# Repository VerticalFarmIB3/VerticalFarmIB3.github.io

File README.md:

Vertical farm - IB3 documentation and webpages

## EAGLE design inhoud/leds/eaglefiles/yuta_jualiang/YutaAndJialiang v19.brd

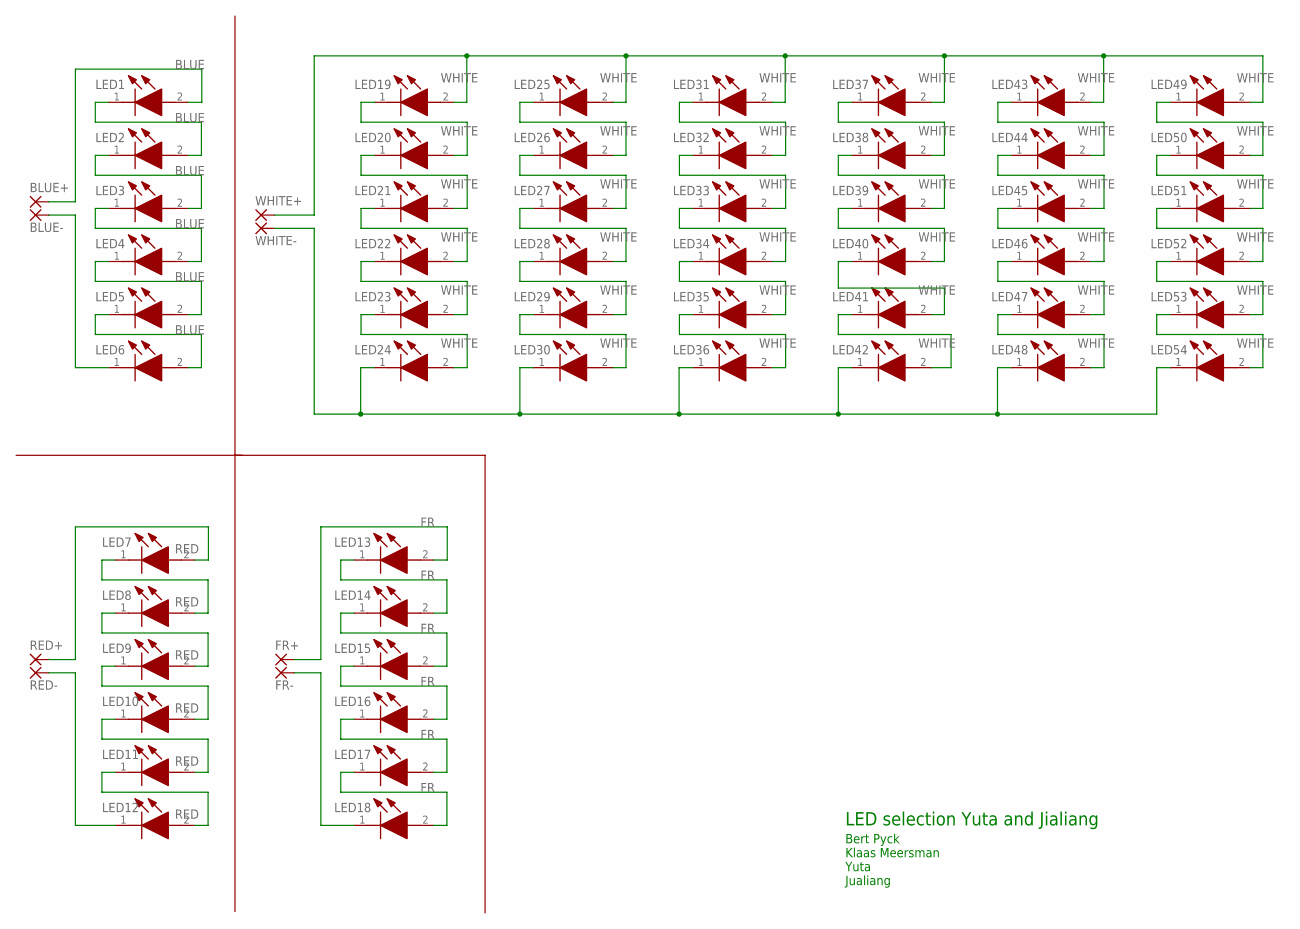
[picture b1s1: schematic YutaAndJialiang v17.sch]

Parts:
BLUE+: SOLDERPAD
BLUE-: SOLDERPAD
FR+: SOLDERPAD
FR-: SOLDERPAD
LED1, LED2, LED3, LED4, LED5, LED6: BLUE; L1SP-PNK1002800000
LED7, LED8, LED9, LED10, LED11, LED12: RED; L1SP-PNK1002800000
LED13, LED14, LED15, LED16, LED17, LED18: FR; L1SP-PNK1002800000
LED19, LED20, LED21, LED22, LED23, LED24, LED25, LED26, LED27, LED28, LED29, LED30, LED31, LED32, LED33, LED34, LED35, LED36, LED37, LED38, LED39, LED40, LED41, LED42, LED43, LED44, LED45, LED46, LED47, LED48, LED49, LED50, LED51, LED52, LED53, LED54: WHITE; L1SP-PNK1002800000
RED+: SOLDERPAD
RED-: SOLDERPAD
WHITE+: SOLDERPAD
WHITE-: SOLDERPAD

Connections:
unnamed: LED7.2 (A), RED+.1
unnamed: LED28.1 (K), LED29.2 (A)
unnamed: LED7.1 (K), LED8.2 (A)
unnamed: LED8.1 (K), LED9.2 (A)
unnamed: LED9.1 (K), LED10.2 (A)
unnamed: LED10.1 (K), LED11.2 (A)
unnamed: LED11.1 (K), LED12.2 (A)
unnamed: BLUE-.1, LED6.1 (K)
unnamed: FR+.1, LED13.2 (A)
unnamed: LED19.2 (A), LED25.2 (A), LED31.2 (A), LED37.2 (A), LED43.2 (A), LED49.2 (A), WHITE+.1
unnamed: LED24.1 (K), LED30.1 (K), LED36.1 (K), LED42.1 (K), LED48.1 (K), LED54.1 (K), WHITE-.1
unnamed: LED19.1 (K), LED20.2 (A)
unnamed: LED29.1 (K), LED30.2 (A)
unnamed: LED20.1 (K), LED21.2 (A)
unnamed: LED21.1 (K), LED22.2 (A)
unnamed: LED22.1 (K), LED23.2 (A)
unnamed: LED13.1 (K), LED14.2 (A)
unnamed: LED14.1 (K), LED15.2 (A)
unnamed: LED15.1 (K), LED16.2 (A)
unnamed: LED16.1 (K), LED17.2 (A)
unnamed: LED17.1 (K), LED18.2 (A)
unnamed: LED23.1 (K), LED24.2 (A)
unnamed: FR-.1, LED18.1 (K)
unnamed: LED25.1 (K), LED26.2 (A)
unnamed: LED26.1 (K), LED27.2 (A)
unnamed: LED27.1 (K), LED28.2 (A)
unnamed: LED12.1 (K), RED-.1
unnamed: LED31.1 (K), LED32.2 (A)
unnamed: LED32.1 (K), LED33.2 (A)
unnamed: BLUE+.1, LED1.2 (A)
unnamed: LED1.1 (K), LED2.2 (A)
unnamed: LED2.1 (K), LED3.2 (A)
unnamed: LED3.1 (K), LED4.2 (A)
unnamed: LED4.1 (K), LED5.2 (A)
unnamed: LED5.1 (K), LED6.2 (A)
unnamed: LED33.1 (K), LED34.2 (A)
unnamed: LED34.1 (K), LED35.2 (A)
unnamed: LED35.1 (K), LED36.2 (A)
unnamed: LED37.1 (K), LED38.2 (A)
unnamed: LED38.1 (K), LED39.2 (A)
unnamed: LED39.1 (K), LED40.2 (A)
unnamed: LED40.1 (K), LED41.2 (A)
unnamed: LED41.1 (K), LED42.2 (A)
unnamed: LED43.1 (K), LED44.2 (A)
unnamed: LED44.1 (K), LED45.2 (A)
unnamed: LED45.1 (K), LED46.2 (A)
unnamed: LED46.1 (K), LED47.2 (A)
unnamed: LED47.1 (K), LED48.2 (A)
unnamed: LED49.1 (K), LED50.2 (A)
unnamed: LED50.1 (K), LED51.2 (A)
unnamed: LED51.1 (K), LED52.2 (A)
unnamed: LED52.1 (K), LED53.2 (A)
unnamed: LED53.1 (K), LED54.2 (A)

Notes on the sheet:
LED selection Yuta and Jialiang
Bert Pyck Klaas Meersman Yuta Jualiang

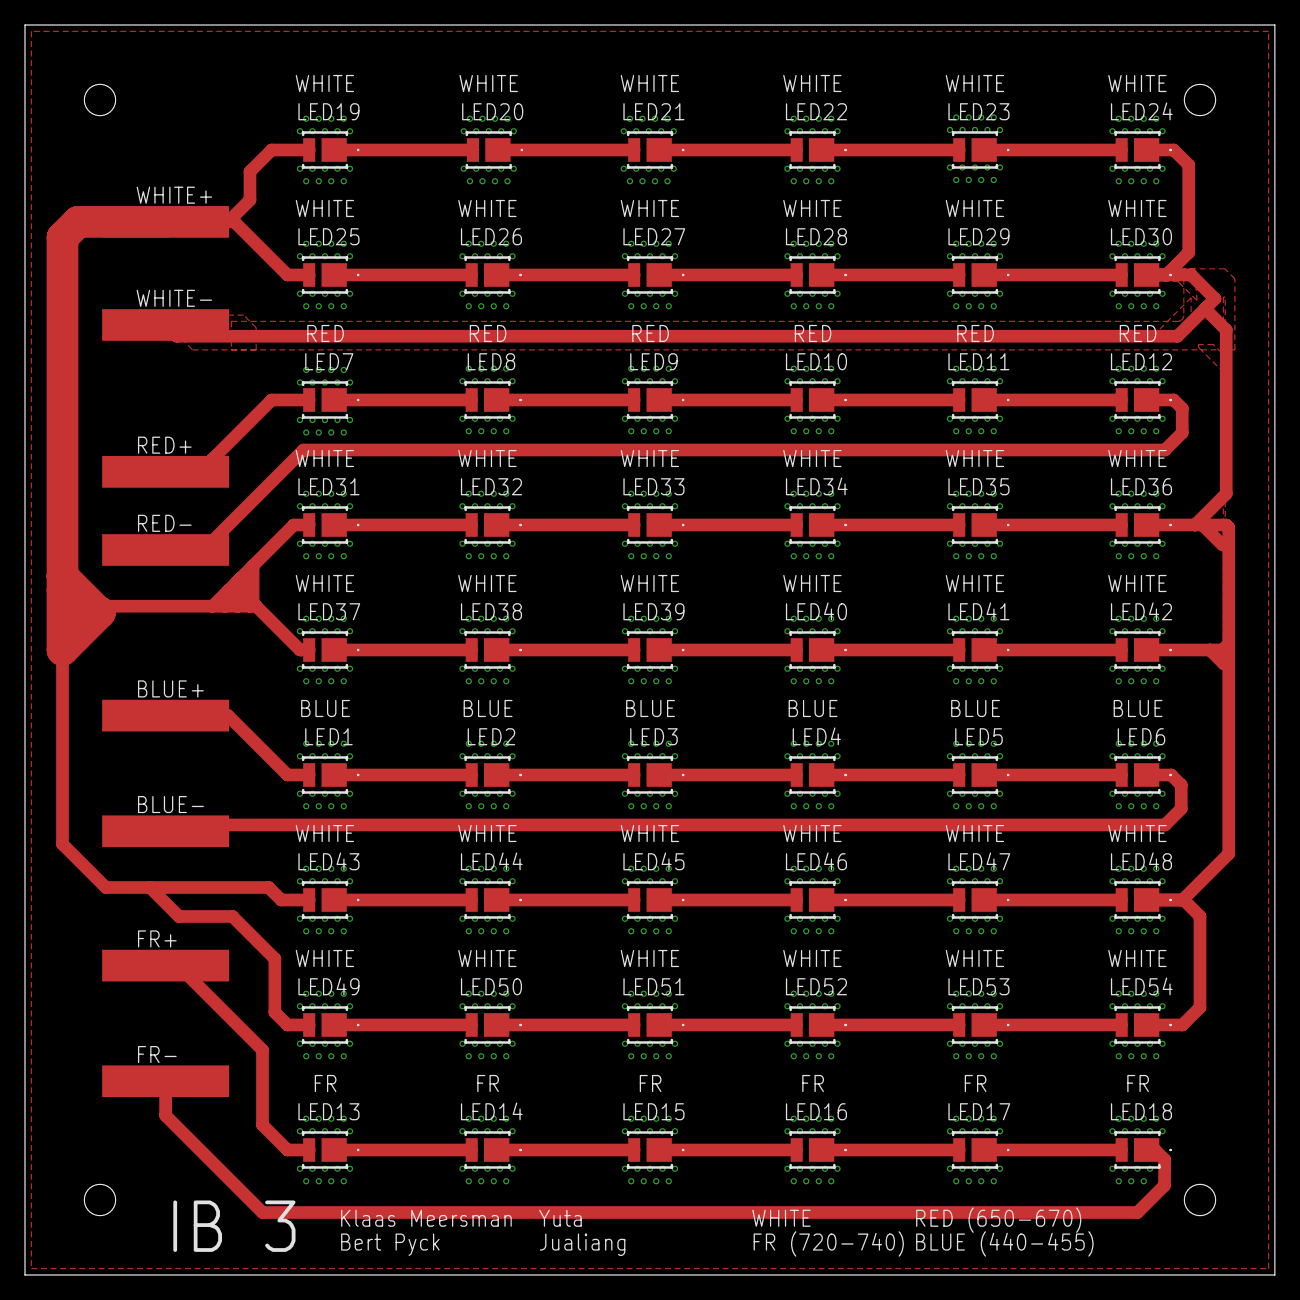
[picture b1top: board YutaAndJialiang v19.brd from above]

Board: 2 copper layers, 100.0 x 100.0 mm, 62 parts (0 on the bottom side), 53 nets.

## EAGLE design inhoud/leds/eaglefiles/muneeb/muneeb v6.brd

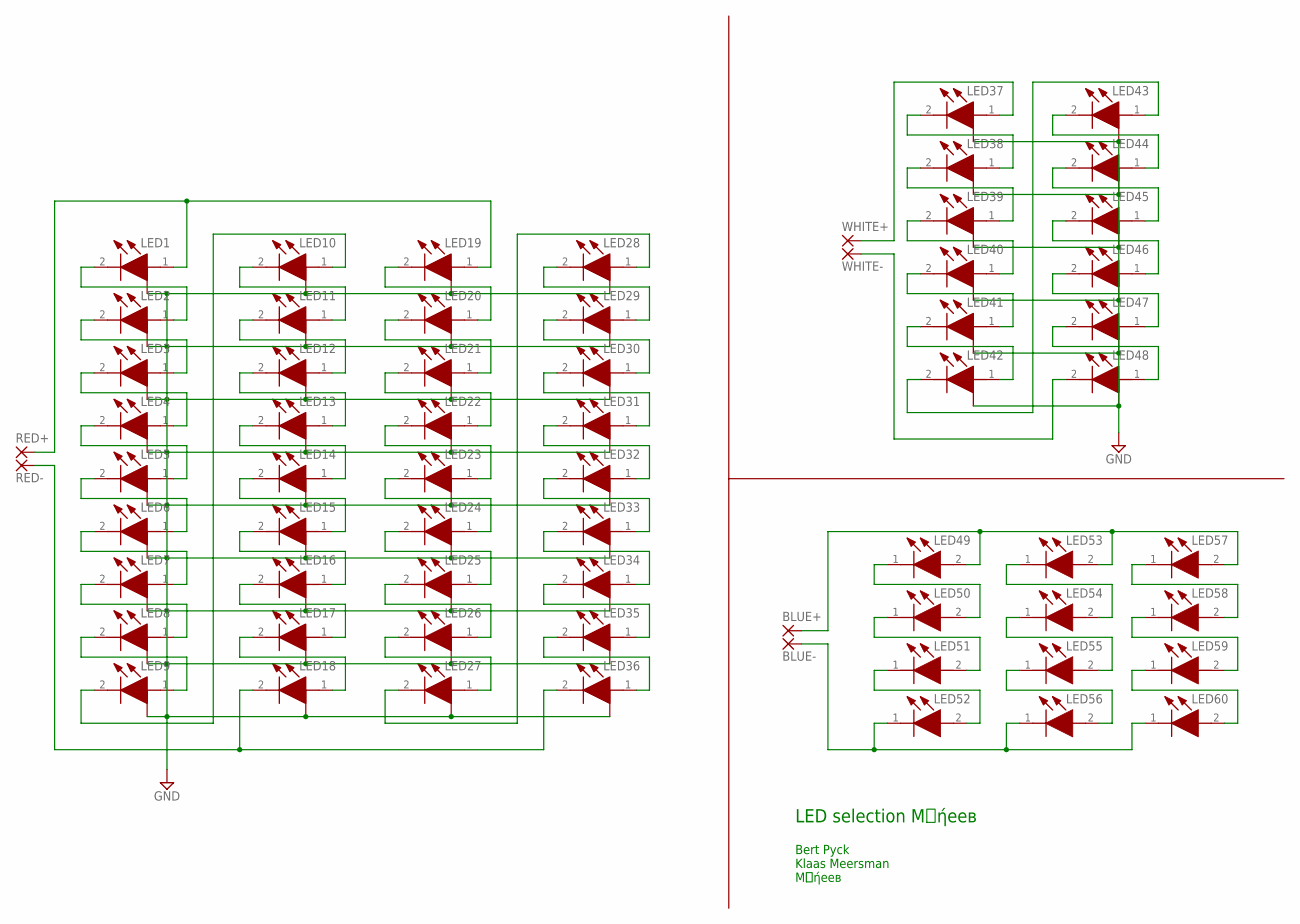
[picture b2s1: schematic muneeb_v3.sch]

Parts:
BLUE+: SOLDERPAD
BLUE-: SOLDERPAD
LED1, LED2, LED3, LED4, LED5, LED6, LED7, LED8, LED9, LED10, LED11, LED12, LED13, LED14, LED15, LED16, LED17, LED18, LED19, LED20, LED21, LED22, LED23, LED24, LED25, LED26, LED27, LED28, LED29, LED30, LED31, LED32, LED33, LED34, LED35, LED36: RED; GR_CSSRML.24
LED37, LED38, LED39, LED40, LED41, LED42, LED43, LED44, LED45, LED46, LED47, LED48: WHITE; GR_CSSRML.24
LED49, LED50, LED51, LED52, LED53, LED54, LED55, LED56, LED57, LED58, LED59, LED60: BLUE; GD_JTLPSI1.14
RED+: SOLDERPAD
RED-: SOLDERPAD
WHITE+: SOLDERPAD
WHITE-: SOLDERPAD

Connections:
GND: LED1.GND, LED1.P$1 (GND), LED1.P$3 (GND), LED1.P$5 (GND), LED1.P$6 (GND), LED1.P$7 (GND), LED1.P$8 (GND), LED1.P$9 (GND), LED1.P$11 (GND), LED1.P$12 (GND), LED1.P$13 (GND), LED1.P$14 (GND), LED1.P$15 (GND), LED2.GND, LED2.P$1 (GND), LED2.P$3 (GND), LED2.P$5 (GND), LED2.P$6 (GND), LED2.P$7 (GND), LED2.P$8 (GND), LED2.P$9 (GND), LED2.P$11 (GND), LED2.P$12 (GND), LED2.P$13 (GND), LED2.P$14 (GND), LED2.P$15 (GND), LED3.GND, LED3.P$1 (GND), LED3.P$3 (GND), LED3.P$5 (GND), LED3.P$6 (GND), LED3.P$7 (GND), LED3.P$8 (GND), LED3.P$9 (GND), LED3.P$11 (GND), LED3.P$12 (GND), LED3.P$13 (GND), LED3.P$14 (GND), LED3.P$15 (GND), LED4.GND, LED4.P$1 (GND), LED4.P$3 (GND), LED4.P$5 (GND), LED4.P$6 (GND), LED4.P$7 (GND), LED4.P$8 (GND), LED4.P$9 (GND), LED4.P$11 (GND), LED4.P$12 (GND), LED4.P$13 (GND), LED4.P$14 (GND), LED4.P$15 (GND), LED5.GND, LED5.P$1 (GND), LED5.P$3 (GND), LED5.P$5 (GND), LED5.P$6 (GND), LED5.P$7 (GND), LED5.P$8 (GND), LED5.P$9 (GND), LED5.P$11 (GND), LED5.P$12 (GND), LED5.P$13 (GND), LED5.P$14 (GND), LED5.P$15 (GND), LED6.GND, LED6.P$1 (GND), LED6.P$3 (GND), LED6.P$5 (GND), LED6.P$6 (GND), LED6.P$7 (GND), LED6.P$8 (GND), LED6.P$9 (GND), LED6.P$11 (GND), LED6.P$12 (GND), LED6.P$13 (GND), LED6.P$14 (GND), LED6.P$15 (GND), LED7.GND, LED7.P$1 (GND), LED7.P$3 (GND), LED7.P$5 (GND), LED7.P$6 (GND), LED7.P$7 (GND), LED7.P$8 (GND), LED7.P$9 (GND), LED7.P$11 (GND), LED7.P$12 (GND), LED7.P$13 (GND), LED7.P$14 (GND), LED7.P$15 (GND), LED8.GND, LED8.P$1 (GND), LED8.P$3 (GND), LED8.P$5 (GND), LED8.P$6 (GND), LED8.P$7 (GND), LED8.P$8 (GND), LED8.P$9 (GND), LED8.P$11 (GND), LED8.P$12 (GND), LED8.P$13 (GND), LED8.P$14 (GND), LED8.P$15 (GND), LED9.GND, LED9.P$1 (GND), LED9.P$3 (GND), LED9.P$5 (GND), LED9.P$6 (GND), LED9.P$7 (GND), LED9.P$8 (GND), LED9.P$9 (GND), LED9.P$11 (GND), LED9.P$12 (GND), LED9.P$13 (GND), LED9.P$14 (GND), LED9.P$15 (GND), LED10.GND, LED10.P$1 (GND), LED10.P$3 (GND), LED10.P$5 (GND), LED10.P$6 (GND), LED10.P$7 (GND), LED10.P$8 (GND), LED10.P$9 (GND), LED10.P$11 (GND), LED10.P$12 (GND), LED10.P$13 (GND), LED10.P$14 (GND), LED10.P$15 (GND), LED11.GND, LED11.P$1 (GND), LED11.P$3 (GND), LED11.P$5 (GND), LED11.P$6 (GND), LED11.P$7 (GND), LED11.P$8 (GND), LED11.P$9 (GND), LED11.P$11 (GND), LED11.P$12 (GND), LED11.P$13 (GND), LED11.P$14 (GND), LED11.P$15 (GND), LED12.GND, LED12.P$1 (GND), LED12.P$3 (GND), LED12.P$5 (GND), LED12.P$6 (GND), LED12.P$7 (GND), LED12.P$8 (GND), LED12.P$9 (GND), LED12.P$11 (GND), LED12.P$12 (GND), LED12.P$13 (GND), LED12.P$14 (GND), LED12.P$15 (GND), LED13.GND, LED13.P$1 (GND), LED13.P$3 (GND), LED13.P$5 (GND), LED13.P$6 (GND), LED13.P$7 (GND), LED13.P$8 (GND), LED13.P$9 (GND), LED13.P$11 (GND), LED13.P$12 (GND), LED13.P$13 (GND), LED13.P$14 (GND), LED13.P$15 (GND), LED14.GND, LED14.P$1 (GND), LED14.P$3 (GND), LED14.P$5 (GND), LED14.P$6 (GND), LED14.P$7 (GND), LED14.P$8 (GND), LED14.P$9 (GND), LED14.P$11 (GND), LED14.P$12 (GND), LED14.P$13 (GND), LED14.P$14 (GND), LED14.P$15 (GND), LED15.GND, LED15.P$1 (GND), LED15.P$3 (GND), LED15.P$5 (GND), LED15.P$6 (GND), LED15.P$7 (GND), LED15.P$8 (GND), LED15.P$9 (GND), LED15.P$11 (GND), LED15.P$12 (GND), LED15.P$13 (GND), LED15.P$14 (GND), LED15.P$15 (GND), LED16.GND, LED16.P$1 (GND), LED16.P$3 (GND), LED16.P$5 (GND), LED16.P$6 (GND), LED16.P$7 (GND), LED16.P$8 (GND), LED16.P$9 (GND), LED16.P$11 (GND), LED16.P$12 (GND), LED16.P$13 (GND), LED16.P$14 (GND), LED16.P$15 (GND), LED17.GND, LED17.P$1 (GND), LED17.P$3 (GND), LED17.P$5 (GND), LED17.P$6 (GND), LED17.P$7 (GND), LED17.P$8 (GND), LED17.P$9 (GND), LED17.P$11 (GND), LED17.P$12 (GND), LED17.P$13 (GND), LED17.P$14 (GND), LED17.P$15 (GND), LED18.GND, LED18.P$1 (GND), LED18.P$3 (GND), LED18.P$5 (GND), LED18.P$6 (GND), LED18.P$7 (GND), LED18.P$8 (GND), LED18.P$9 (GND), LED18.P$11 (GND), LED18.P$12 (GND), LED18.P$13 (GND), LED18.P$14 (GND), LED18.P$15 (GND), LED19.GND, LED19.P$1 (GND), LED19.P$3 (GND), LED19.P$5 (GND), LED19.P$6 (GND), LED19.P$7 (GND), LED19.P$8 (GND), LED19.P$9 (GND), LED19.P$11 (GND), LED19.P$12 (GND), LED19.P$13 (GND), LED19.P$14 (GND), LED19.P$15 (GND), LED20.GND, LED20.P$1 (GND), LED20.P$3 (GND), LED20.P$5 (GND), LED20.P$6 (GND), LED20.P$7 (GND), LED20.P$8 (GND), LED20.P$9 (GND), LED20.P$11 (GND), LED20.P$12 (GND), LED20.P$13 (GND), LED20.P$14 (GND), LED20.P$15 (GND), LED21.GND, LED21.P$1 (GND), LED21.P$3 (GND), LED21.P$5 (GND), LED21.P$6 (GND), LED21.P$7 (GND), LED21.P$8 (GND), LED21.P$9 (GND), LED21.P$11 (GND), LED21.P$12 (GND), LED21.P$13 (GND), LED21.P$14 (GND), LED21.P$15 (GND), LED22.GND, LED22.P$1 (GND), LED22.P$3 (GND), LED22.P$5 (GND), LED22.P$6 (GND), LED22.P$7 (GND), LED22.P$8 (GND), LED22.P$9 (GND), LED22.P$11 (GND), LED22.P$12 (GND), LED22.P$13 (GND), LED22.P$14 (GND), LED22.P$15 (GND), LED23.GND, LED23.P$1 (GND), LED23.P$3 (GND), LED23.P$5 (GND), LED23.P$6 (GND), LED23.P$7 (GND), LED23.P$8 (GND), LED23.P$9 (GND), LED23.P$11 (GND), LED23.P$12 (GND), LED23.P$13 (GND), LED23.P$14 (GND), LED23.P$15 (GND), LED24.GND, LED24.P$1 (GND), LED24.P$3 (GND), LED24.P$5 (GND), LED24.P$6 (GND), LED24.P$7 (GND), LED24.P$8 (GND), LED24.P$9 (GND), LED24.P$11 (GND), LED24.P$12 (GND), LED24.P$13 (GND), LED24.P$14 (GND), LED24.P$15 (GND), LED25.GND, LED25.P$1 (GND), LED25.P$3 (GND), LED25.P$5 (GND), LED25.P$6 (GND), LED25.P$7 (GND), LED25.P$8 (GND), LED25.P$9 (GND), LED25.P$11 (GND), LED25.P$12 (GND), LED25.P$13 (GND), LED25.P$14 (GND), LED25.P$15 (GND), LED26.GND, LED26.P$1 (GND), LED26.P$3 (GND), LED26.P$5 (GND), LED26.P$6 (GND), LED26.P$7 (GND), LED26.P$8 (GND), LED26.P$9 (GND), LED26.P$11 (GND), LED26.P$12 (GND), LED26.P$13 (GND), LED26.P$14 (GND), LED26.P$15 (GND), LED27.GND, LED27.P$1 (GND), LED27.P$3 (GND), LED27.P$5 (GND), LED27.P$6 (GND), LED27.P$7 (GND), LED27.P$8 (GND), LED27.P$9 (GND), LED27.P$11 (GND), LED27.P$12 (GND), LED27.P$13 (GND), LED27.P$14 (GND), LED27.P$15 (GND), LED28.GND, LED28.P$1 (GND), LED28.P$3 (GND), LED28.P$5 (GND), LED28.P$6 (GND), LED28.P$7 (GND), LED28.P$8 (GND), LED28.P$9 (GND), LED28.P$11 (GND), LED28.P$12 (GND), LED28.P$13 (GND), LED28.P$14 (GND), LED28.P$15 (GND), LED29.GND, LED29.P$1 (GND), LED29.P$3 (GND), LED29.P$5 (GND), LED29.P$6 (GND), LED29.P$7 (GND), LED29.P$8 (GND), LED29.P$9 (GND), LED29.P$11 (GND), LED29.P$12 (GND), LED29.P$13 (GND), LED29.P$14 (GND), LED29.P$15 (GND), LED30.GND, LED30.P$1 (GND), LED30.P$3 (GND), LED30.P$5 (GND), LED30.P$6 (GND), LED30.P$7 (GND), LED30.P$8 (GND), LED30.P$9 (GND), LED30.P$11 (GND), LED30.P$12 (GND), LED30.P$13 (GND), LED30.P$14 (GND), LED30.P$15 (GND), LED31.GND, LED31.P$1 (GND), LED31.P$3 (GND), LED31.P$5 (GND), LED31.P$6 (GND), LED31.P$7 (GND), LED31.P$8 (GND), LED31.P$9 (GND), LED31.P$11 (GND), LED31.P$12 (GND), LED31.P$13 (GND), LED31.P$14 (GND), LED31.P$15 (GND), LED32.GND, LED32.P$1 (GND), LED32.P$3 (GND), LED32.P$5 (GND), LED32.P$6 (GND), LED32.P$7 (GND), LED32.P$8 (GND), LED32.P$9 (GND), LED32.P$11 (GND), LED32.P$12 (GND), LED32.P$13 (GND), LED32.P$14 (GND), LED32.P$15 (GND), LED33.GND, LED33.P$1 (GND), LED33.P$3 (GND), LED33.P$5 (GND), LED33.P$6 (GND), LED33.P$7 (GND), LED33.P$8 (GND), LED33.P$9 (GND), LED33.P$11 (GND), LED33.P$12 (GND), LED33.P$13 (GND), LED33.P$14 (GND), LED33.P$15 (GND), LED34.GND, LED34.P$1 (GND), LED34.P$3 (GND), LED34.P$5 (GND), LED34.P$6 (GND), LED34.P$7 (GND), LED34.P$8 (GND), LED34.P$9 (GND), LED34.P$11 (GND), LED34.P$12 (GND), LED34.P$13 (GND), LED34.P$14 (GND), LED34.P$15 (GND), LED35.GND, LED35.P$1 (GND), LED35.P$3 (GND), LED35.P$5 (GND), LED35.P$6 (GND), LED35.P$7 (GND), LED35.P$8 (GND), LED35.P$9 (GND), LED35.P$11 (GND), LED35.P$12 (GND)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
unnamed: LED1.1 (A), LED19.1 (A), RED+.1
unnamed: LED1.2 (K), LED2.1 (A)
unnamed: LED37.1 (A), WHITE+.1
unnamed: LED48.2 (K), WHITE-.1
unnamed: LED37.2 (K), LED38.1 (A)
unnamed: LED38.2 (K), LED39.1 (A)
unnamed: LED39.2 (K), LED40.1 (A)
unnamed: LED40.2 (K), LED41.1 (A)
unnamed: LED41.2 (K), LED42.1 (A)
unnamed: LED42.2 (K), LED43.1 (A)
unnamed: LED2.2 (K), LED3.1 (A)
unnamed: LED3.2 (K), LED4.1 (A)
unnamed: LED4.2 (K), LED5.1 (A)
unnamed: LED5.2 (K), LED6.1 (A)
unnamed: LED6.2 (K), LED7.1 (A)
unnamed: LED43.2 (K), LED44.1 (A)
unnamed: LED44.2 (K), LED45.1 (A)
unnamed: LED45.2 (K), LED46.1 (A)
unnamed: LED46.2 (K), LED47.1 (A)
unnamed: BLUE+.1, LED49.2 (A), LED53.2 (A), LED57.2 (A)
unnamed: LED7.2 (K), LED8.1 (A)
unnamed: BLUE-.1, LED52.1 (K), LED56.1 (K), LED60.1 (K)
unnamed: LED8.2 (K), LED9.1 (A)
unnamed: LED10.2 (K), LED11.1 (A)
unnamed: LED11.2 (K), LED12.1 (A)
unnamed: LED12.2 (K), LED13.1 (A)
unnamed: LED13.2 (K), LED14.1 (A)
unnamed: LED49.1 (K), LED50.2 (A)
unnamed: LED19.2 (K), LED20.1 (A)
unnamed: LED20.2 (K), LED21.1 (A)
unnamed: LED50.1 (K), LED51.2 (A)
unnamed: LED51.1 (K), LED52.2 (A)
unnamed: LED53.1 (K), LED54.2 (A)
unnamed: LED14.2 (K), LED15.1 (A)
unnamed: LED15.2 (K), LED16.1 (A)
unnamed: LED16.2 (K), LED17.1 (A)
unnamed: LED17.2 (K), LED18.1 (A)
unnamed: LED54.1 (K), LED55.2 (A)
unnamed: LED55.1 (K), LED56.2 (A)
unnamed: LED57.1 (K), LED58.2 (A)
unnamed: LED58.1 (K), LED59.2 (A)
unnamed: LED59.1 (K), LED60.2 (A)
unnamed: LED47.2 (K), LED48.1 (A)
unnamed: LED18.2 (K), LED36.2 (K), RED-.1
unnamed: LED9.2 (K), LED10.1 (A)
unnamed: LED21.2 (K), LED22.1 (A)
unnamed: LED22.2 (K), LED23.1 (A)
unnamed: LED23.2 (K), LED24.1 (A)
unnamed: LED24.2 (K), LED25.1 (A)
unnamed: LED25.2 (K), LED26.1 (A)
unnamed: LED26.2 (K), LED27.1 (A)
unnamed: LED28.2 (K), LED29.1 (A)
unnamed: LED29.2 (K), LED30.1 (A)
unnamed: LED30.2 (K), LED31.1 (A)
unnamed: LED31.2 (K), LED32.1 (A)
unnamed: LED32.2 (K), LED33.1 (A)
unnamed: LED33.2 (K), LED34.1 (A)
unnamed: LED34.2 (K), LED35.1 (A)
unnamed: LED35.2 (K), LED36.1 (A)
unnamed: LED27.2 (K), LED28.1 (A)

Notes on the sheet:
LED selection M𝔲ήeeв
Bert Pyck Klaas Meersman M𝔲ήeeв

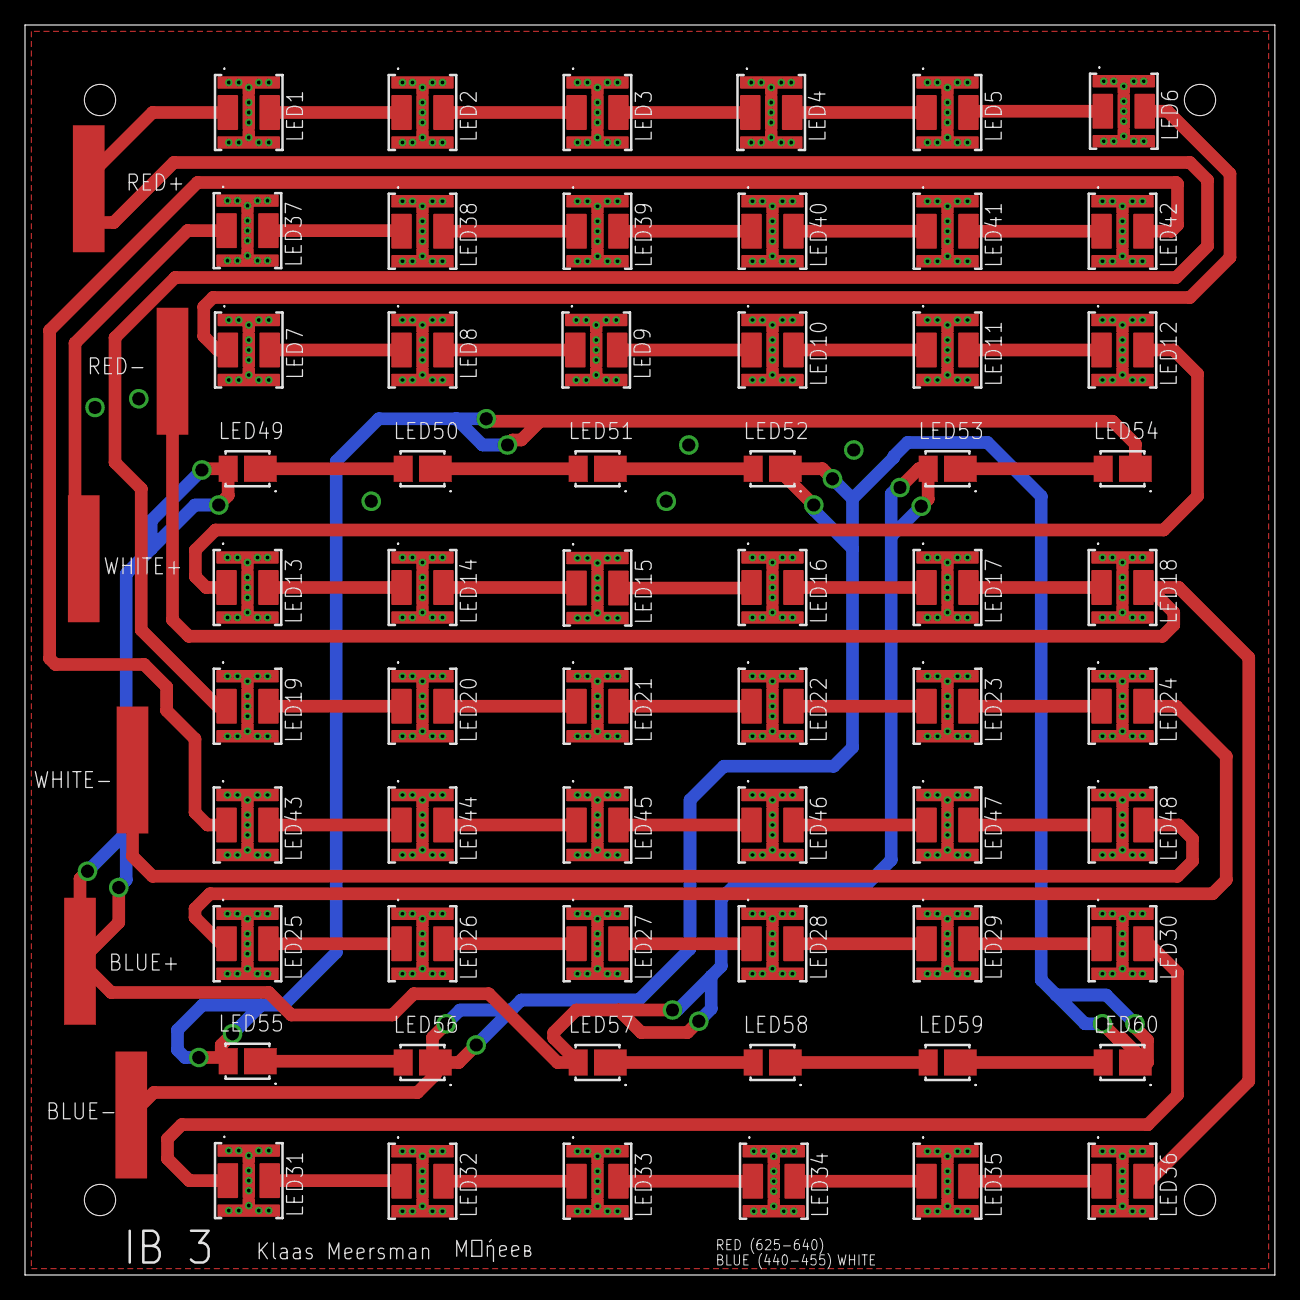
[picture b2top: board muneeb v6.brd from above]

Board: 2 copper layers, 100.0 x 100.0 mm, 66 parts (0 on the bottom side), 61 nets.

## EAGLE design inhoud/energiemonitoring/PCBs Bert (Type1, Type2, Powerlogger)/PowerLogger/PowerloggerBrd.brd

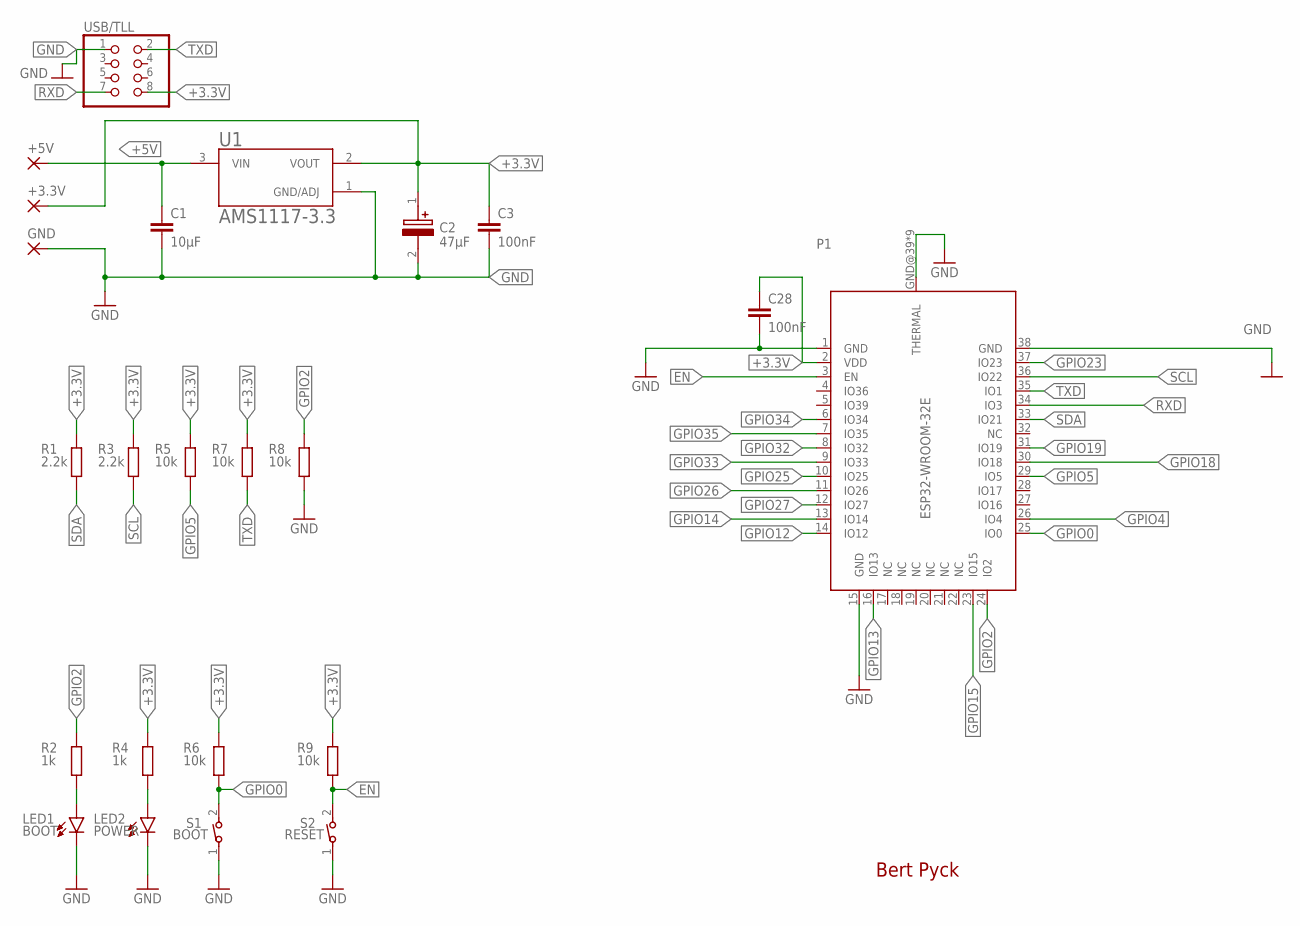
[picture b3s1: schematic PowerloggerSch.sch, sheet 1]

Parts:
+3.3V, +5V: SOLDERPAD
C1: 10µF; C1206
C2: 47µF; CAPAE660X550N
C3, C28: 100nF; C1206
GND: SOLDERPAD
LED1: BOOT; CHIPLED_1206
LED2: POWER; CHIPLED_1206
P1: ESP32-WROOM-32E
R1, R3: 2.2k; R1206
R2, R4: 1k; R1206
R5, R6, R7, R8, R9: 10k; R1206
S1: BOOT; 434111043826
S2: RESET; 434111043826
U1: AMS1117-3.3; SOT229P700X180-4N
USB/TLL: PINHD-2X4; 2X04

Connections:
+3.3V: +3.3V.1, C2.1 (+), C3.1, C28.1, P1.2 (VDD), R1.2, R3.2, R4.2, R5.2, R6.2, R7.2, R9.2, U1.2 (VOUT), USB/TLL.8; also elsewhere on the board
+5V: +5V.1, C1.1, U1.3 (VIN); also elsewhere on the board
EN: P1.3 (EN), R9.1, S2.2
GND: C1.2, C2.2 (-), C3.2, C28.2, GND.1, LED1.C, LED2.C, P1.1 (GND), P1.15 (GND), P1.38 (GND), P1.GND@39 (THERMAL), P1.GND@40 (THERMAL), P1.GND@41 (THERMAL), P1.GND@42 (THERMAL), P1.GND@43 (THERMAL), P1.GND@44 (THERMAL), P1.GND@45 (THERMAL), P1.GND@46 (THERMAL), P1.GND@47 (THERMAL), R8.1, S1.1, S2.1, U1.1 (GND/ADJ), USB/TLL.1; also elsewhere on the board
GPIO0: P1.25 (IO0), R6.1, S1.2
GPIO2: P1.24 (IO2), R2.2, R8.2
GPIO4: P1.26 (IO4)
GPIO5: P1.29 (IO5), R5.1
GPIO12: P1.14 (IO12)
GPIO13: P1.16 (IO13)
GPIO14: P1.13 (IO14)
GPIO15: P1.23 (IO15)
GPIO18: P1.30 (IO18); also elsewhere on the board
GPIO19: P1.31 (IO19); also elsewhere on the board
GPIO23: P1.37 (IO23); also elsewhere on the board
GPIO25: P1.10 (IO25)
GPIO26: P1.11 (IO26)
GPIO27: P1.12 (IO27)
GPIO32: P1.8 (IO32)
GPIO33: P1.9 (IO33)
GPIO34: P1.6 (IO34)
GPIO35: P1.7 (IO35)
unnamed: LED1.A, R2.1
unnamed: LED2.A, R4.1
RXD: P1.34 (IO3), USB/TLL.7
SCL: P1.36 (IO22), R3.1; also elsewhere on the board
SDA: P1.33 (IO21), R1.1; also elsewhere on the board
TXD: P1.35 (IO1), R7.1, USB/TLL.2

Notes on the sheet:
Bert Pyck

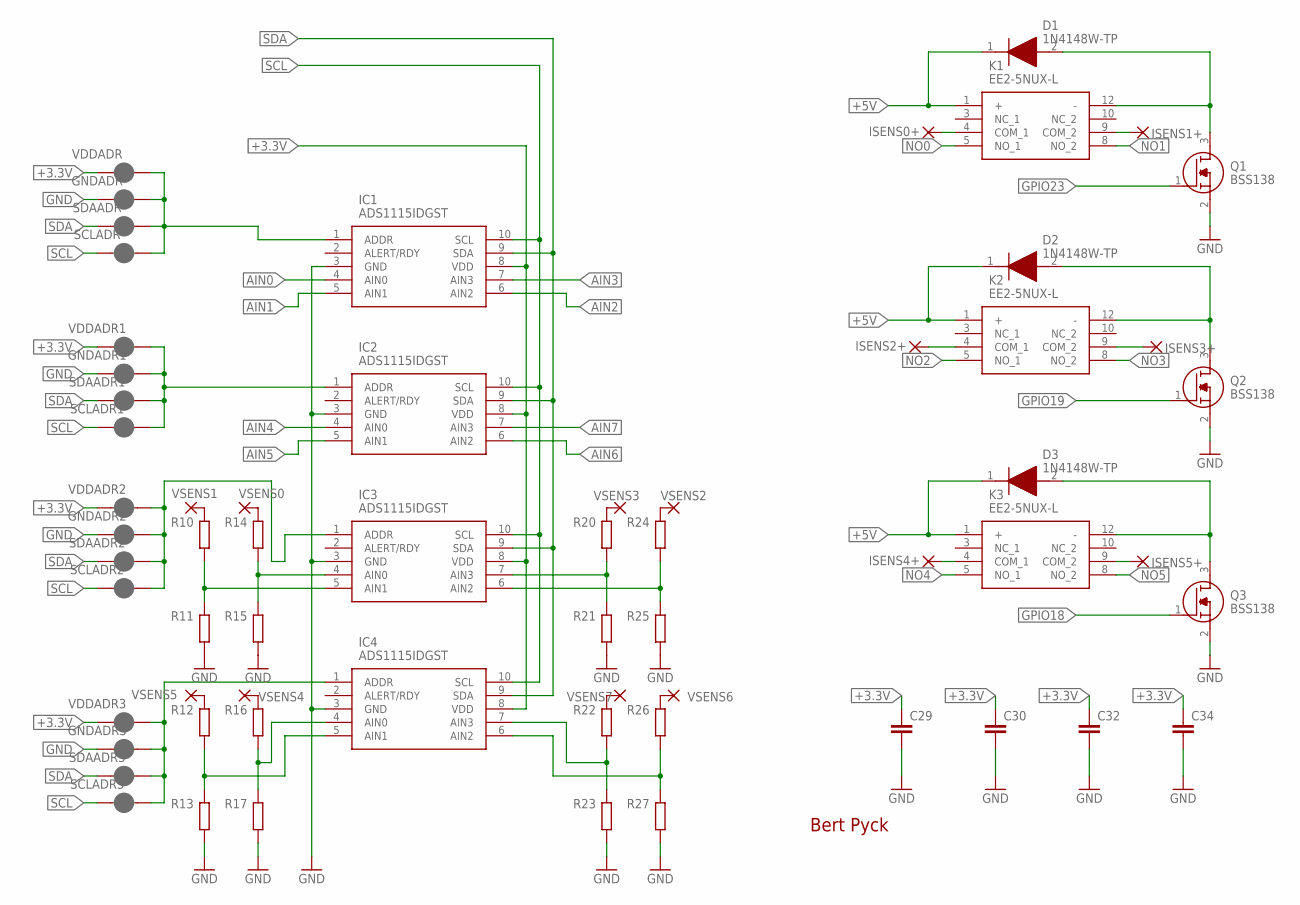
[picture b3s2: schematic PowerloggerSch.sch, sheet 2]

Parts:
C29, C30, C32, C34: 100nF; C1206
D1, D2, D3: 1N4148W-TP; SOD3715X135N
GNDADR, GNDADR1, GNDADR2, GNDADR3: JUMPER-SMT_2_NC_PASTE_SILK; SMT-JUMPER_2_NC_PASTE_SILK
IC1, IC2, IC3, IC4: ADS1115IDGST; SOP50P490X110-10N
ISENS0+, ISENS1+, ISENS2+, ISENS3+, ISENS4+, ISENS5+: SOLDERPAD
K1, K2, K3: EE2-5NUX-L; EE25NUXL
Q1, Q2, Q3: BSS138; SOT95P240X120-3N
R10, R11, R12, R13, R14, R15, R16, R17, R20, R21, R22, R23, R24, R25, R26, R27: R-EU_R1206; R1206
SCLADR, SCLADR1, SCLADR2, SCLADR3: JUMPER-SMT_2_NC_PASTE_SILK; SMT-JUMPER_2_NC_PASTE_SILK
SDAADR, SDAADR1, SDAADR2, SDAADR3: JUMPER-SMT_2_NC_PASTE_SILK; SMT-JUMPER_2_NC_PASTE_SILK
VDDADR, VDDADR1, VDDADR2, VDDADR3: JUMPER-SMT_2_NC_PASTE_SILK; SMT-JUMPER_2_NC_PASTE_SILK
VSENS0, VSENS1, VSENS2, VSENS3, VSENS4, VSENS5, VSENS6, VSENS7: SOLDERPAD

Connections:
+3.3V: C29.1, C30.1, C32.1, C34.1, IC1.8 (VDD), IC2.8 (VDD), IC3.8 (VDD), IC4.8 (VDD), VDDADR.1, VDDADR1.1, VDDADR2.1, VDDADR3.1; also elsewhere on the board
+5V: D1.1 (K), D2.1 (K), D3.1 (K), K1.1 (+), K2.1 (+), K3.1 (+); also elsewhere on the board
AIN0: IC1.4 (AIN0); also elsewhere on the board
AIN1: IC1.5 (AIN1); also elsewhere on the board
AIN2: IC1.6 (AIN2); also elsewhere on the board
AIN3: IC1.7 (AIN3); also elsewhere on the board
AIN4: IC2.4 (AIN0); also elsewhere on the board
AIN5: IC2.5 (AIN1); also elsewhere on the board
AIN6: IC2.6 (AIN2); also elsewhere on the board
AIN7: IC2.7 (AIN3); also elsewhere on the board
GND: C29.2, C30.2, C32.2, C34.2, GNDADR.1, GNDADR1.1, GNDADR2.1, GNDADR3.1, IC1.3 (GND), IC2.3 (GND), IC3.3 (GND), IC4.3 (GND), Q1.2 (S), Q2.2 (S), Q3.2 (S), R11.1, R13.1, R15.1, R17.1, R21.1, R23.1, R25.1, R27.1; also elsewhere on the board
GPIO18: Q3.1 (G); also elsewhere on the board
GPIO19: Q2.1 (G); also elsewhere on the board
GPIO23: Q1.1 (G); also elsewhere on the board
unnamed: D1.2 (A), K1.12 (-), Q1.3 (D)
unnamed: ISENS0+.1, K1.4 (COM_1)
unnamed: ISENS2+.1, K2.4 (COM_1)
unnamed: IC3.4 (AIN0), R14.1, R15.2
unnamed: ISENS1+.1, K1.9 (COM_2)
unnamed: ISENS3+.1, K2.9 (COM_2)
unnamed: D2.2 (A), K2.12 (-), Q2.3 (D)
unnamed: IC3.5 (AIN1), R10.1, R11.2
unnamed: IC4.4 (AIN0), R16.1, R17.2
unnamed: IC4.5 (AIN1), R12.1, R13.2
unnamed: IC3.7 (AIN3), R20.1, R21.2
unnamed: IC3.6 (AIN2), R24.1, R25.2
unnamed: IC4.7 (AIN3), R22.1, R23.2
unnamed: D3.2 (A), K3.12 (-), Q3.3 (D)
unnamed: IC4.6 (AIN2), R26.1, R27.2
unnamed: ISENS4+.1, K3.4 (COM_1)
unnamed: R10.2, VSENS1.1
unnamed: R14.2, VSENS0.1
unnamed: ISENS5+.1, K3.9 (COM_2)
unnamed: R20.2, VSENS3.1
unnamed: GNDADR.2, IC1.1 (ADDR), SCLADR.2, SDAADR.2, VDDADR.2
unnamed: GNDADR1.2, IC2.1 (ADDR), SCLADR1.2, SDAADR1.2, VDDADR1.2
unnamed: R24.2, VSENS2.1
unnamed: R12.2, VSENS5.1
unnamed: R16.2, VSENS4.1
unnamed: R22.2, VSENS7.1
unnamed: R26.2, VSENS6.1
unnamed: GNDADR3.2, IC4.1 (ADDR), SCLADR3.2, SDAADR3.2, VDDADR3.2
unnamed: GNDADR2.2, IC3.1 (ADDR), SCLADR2.2, SDAADR2.2, VDDADR2.2
NO0: K1.5 (NO_1); also elsewhere on the board
NO1: K1.8 (NO_2); also elsewhere on the board
NO2: K2.5 (NO_1); also elsewhere on the board
NO3: K2.8 (NO_2); also elsewhere on the board
NO4: K3.5 (NO_1); also elsewhere on the board
NO5: K3.8 (NO_2); also elsewhere on the board
SCL: IC1.10 (SCL), IC2.10 (SCL), IC3.10 (SCL), IC4.10 (SCL), SCLADR.1, SCLADR1.1, SCLADR2.1, SCLADR3.1; also elsewhere on the board
SDA: IC1.9 (SDA), IC2.9 (SDA), IC3.9 (SDA), IC4.9 (SDA), SDAADR.1, SDAADR1.1, SDAADR2.1, SDAADR3.1; also elsewhere on the board

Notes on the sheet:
Bert Pyck

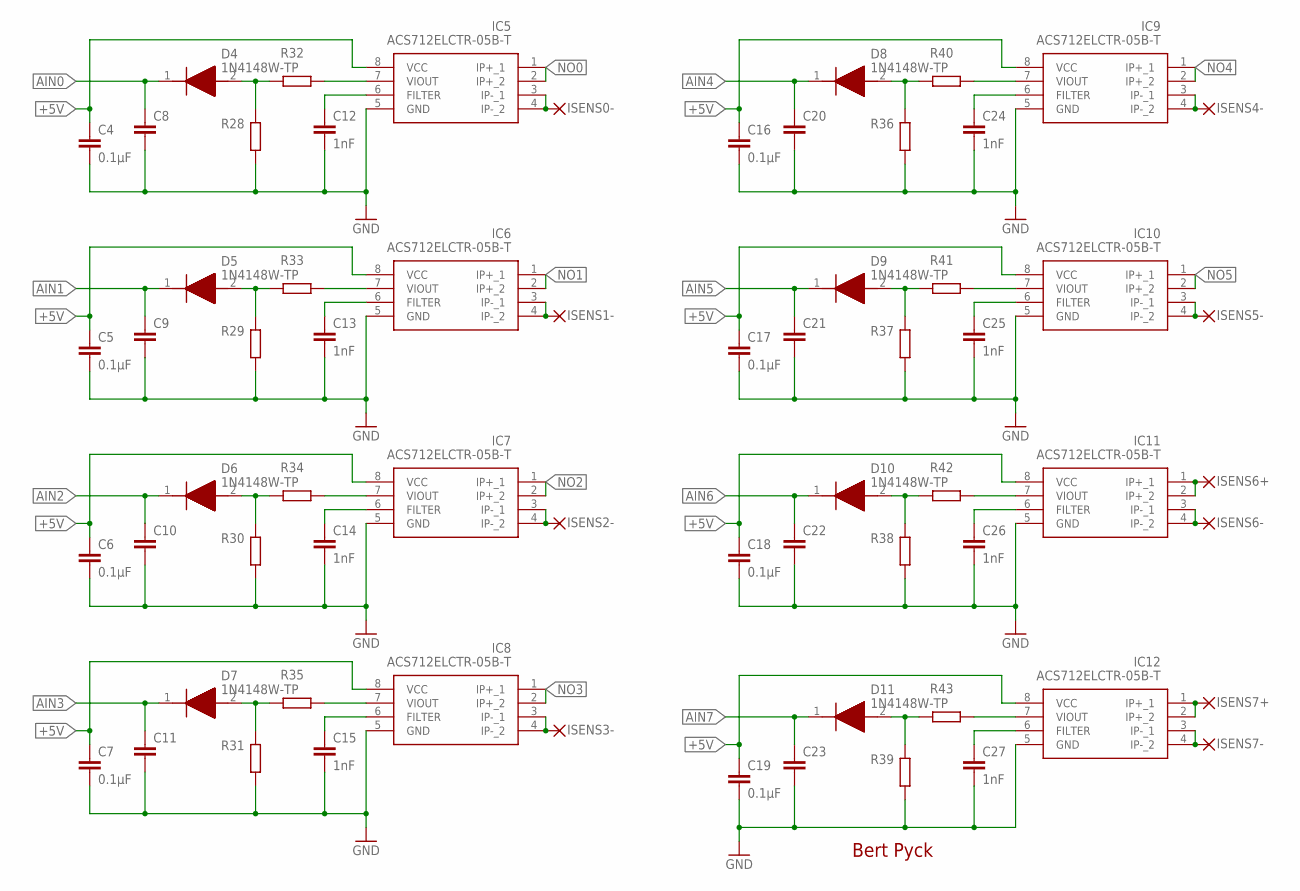
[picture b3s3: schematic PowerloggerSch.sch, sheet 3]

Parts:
C4, C5, C6, C7, C16, C17, C18, C19: 0.1µF; C1206
C8, C9, C10, C11, C20, C21, C22, C23: C-EUC1206; C1206
C12, C13, C14, C15, C24, C25, C26, C27: 1nF; C1206
D4, D5, D6, D7, D8, D9, D10, D11: 1N4148W-TP; SOD3715X135N
IC5, IC6, IC7, IC8, IC9, IC10, IC11, IC12: ACS712ELCTR-05B-T; SOIC127P600X175-8N
ISENS0-, ISENS1-, ISENS2-, ISENS3-, ISENS4-, ISENS5-, ISENS6+, ISENS6-, ISENS7+, ISENS7-: SOLDERPAD
R28, R29, R30, R31, R32, R33, R34, R35, R36, R37, R38, R39, R40, R41, R42, R43: R-EU_R1206; R1206

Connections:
+5V: C4.1, C5.1, C6.1, C7.1, C16.1, C17.1, C18.1, C19.1, IC5.8 (VCC), IC6.8 (VCC), IC7.8 (VCC), IC8.8 (VCC), IC9.8 (VCC), IC10.8 (VCC), IC11.8 (VCC), IC12.8 (VCC); also elsewhere on the board
AIN0: C8.1, D4.1 (K); also elsewhere on the board
AIN1: C9.1, D5.1 (K); also elsewhere on the board
AIN2: C10.1, D6.1 (K); also elsewhere on the board
AIN3: C11.1, D7.1 (K); also elsewhere on the board
AIN4: C20.1, D8.1 (K); also elsewhere on the board
AIN5: C21.1, D9.1 (K); also elsewhere on the board
AIN6: C22.1, D10.1 (K); also elsewhere on the board
AIN7: C23.1, D11.1 (K); also elsewhere on the board
GND: C4.2, C5.2, C6.2, C7.2, C8.2, C9.2, C10.2, C11.2, C12.2, C13.2, C14.2, C15.2, C16.2, C17.2, C18.2, C19.2, C20.2, C21.2, C22.2, C23.2, C24.2, C25.2, C26.2, C27.2, IC5.5 (GND), IC6.5 (GND), IC7.5 (GND), IC8.5 (GND), IC9.5 (GND), IC10.5 (GND), IC11.5 (GND), IC12.5 (GND), R28.1, R29.1, R30.1, R31.1, R36.1, R37.1, R38.1, R39.1; also elsewhere on the board
unnamed: C12.1, IC5.6 (FILTER)
unnamed: IC5.7 (VIOUT), R32.1
unnamed: D4.2 (A), R28.2, R32.2
unnamed: C13.1, IC6.6 (FILTER)
unnamed: IC5.3 (IP-_1), IC5.4 (IP-_2), ISENS0-.1
unnamed: IC6.7 (VIOUT), R33.1
unnamed: D5.2 (A), R29.2, R33.2
unnamed: IC6.3 (IP-_1), IC6.4 (IP-_2), ISENS1-.1
unnamed: C14.1, IC7.6 (FILTER)
unnamed: IC7.7 (VIOUT), R34.1
unnamed: D6.2 (A), R30.2, R34.2
unnamed: IC7.3 (IP-_1), IC7.4 (IP-_2), ISENS2-.1
unnamed: C15.1, IC8.6 (FILTER)
unnamed: IC8.7 (VIOUT), R35.1
unnamed: D7.2 (A), R31.2, R35.2
unnamed: IC8.3 (IP-_1), IC8.4 (IP-_2), ISENS3-.1
unnamed: C24.1, IC9.6 (FILTER)
unnamed: IC9.7 (VIOUT), R40.1
unnamed: D8.2 (A), R36.2, R40.2
unnamed: IC9.3 (IP-_1), IC9.4 (IP-_2), ISENS4-.1
unnamed: C25.1, IC10.6 (FILTER)
unnamed: IC10.7 (VIOUT), R41.1
unnamed: D9.2 (A), R37.2, R41.2
unnamed: IC10.3 (IP-_1), IC10.4 (IP-_2), ISENS5-.1
unnamed: C26.1, IC11.6 (FILTER)
unnamed: IC11.7 (VIOUT), R42.1
unnamed: D10.2 (A), R38.2, R42.2
unnamed: IC11.1 (IP+_1), IC11.2 (IP+_2), ISENS6+.1
unnamed: IC11.3 (IP-_1), IC11.4 (IP-_2), ISENS6-.1
unnamed: C27.1, IC12.6 (FILTER)
unnamed: IC12.7 (VIOUT), R43.1
unnamed: D11.2 (A), R39.2, R43.2
unnamed: IC12.1 (IP+_1), IC12.2 (IP+_2), ISENS7+.1
unnamed: IC12.3 (IP-_1), IC12.4 (IP-_2), ISENS7-.1
NO0: IC5.1 (IP+_1), IC5.2 (IP+_2); also elsewhere on the board
NO1: IC6.1 (IP+_1), IC6.2 (IP+_2); also elsewhere on the board
NO2: IC7.1 (IP+_1), IC7.2 (IP+_2); also elsewhere on the board
NO3: IC8.1 (IP+_1), IC8.2 (IP+_2); also elsewhere on the board
NO4: IC9.1 (IP+_1), IC9.2 (IP+_2); also elsewhere on the board
NO5: IC10.1 (IP+_1), IC10.2 (IP+_2); also elsewhere on the board

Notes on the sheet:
Bert Pyck

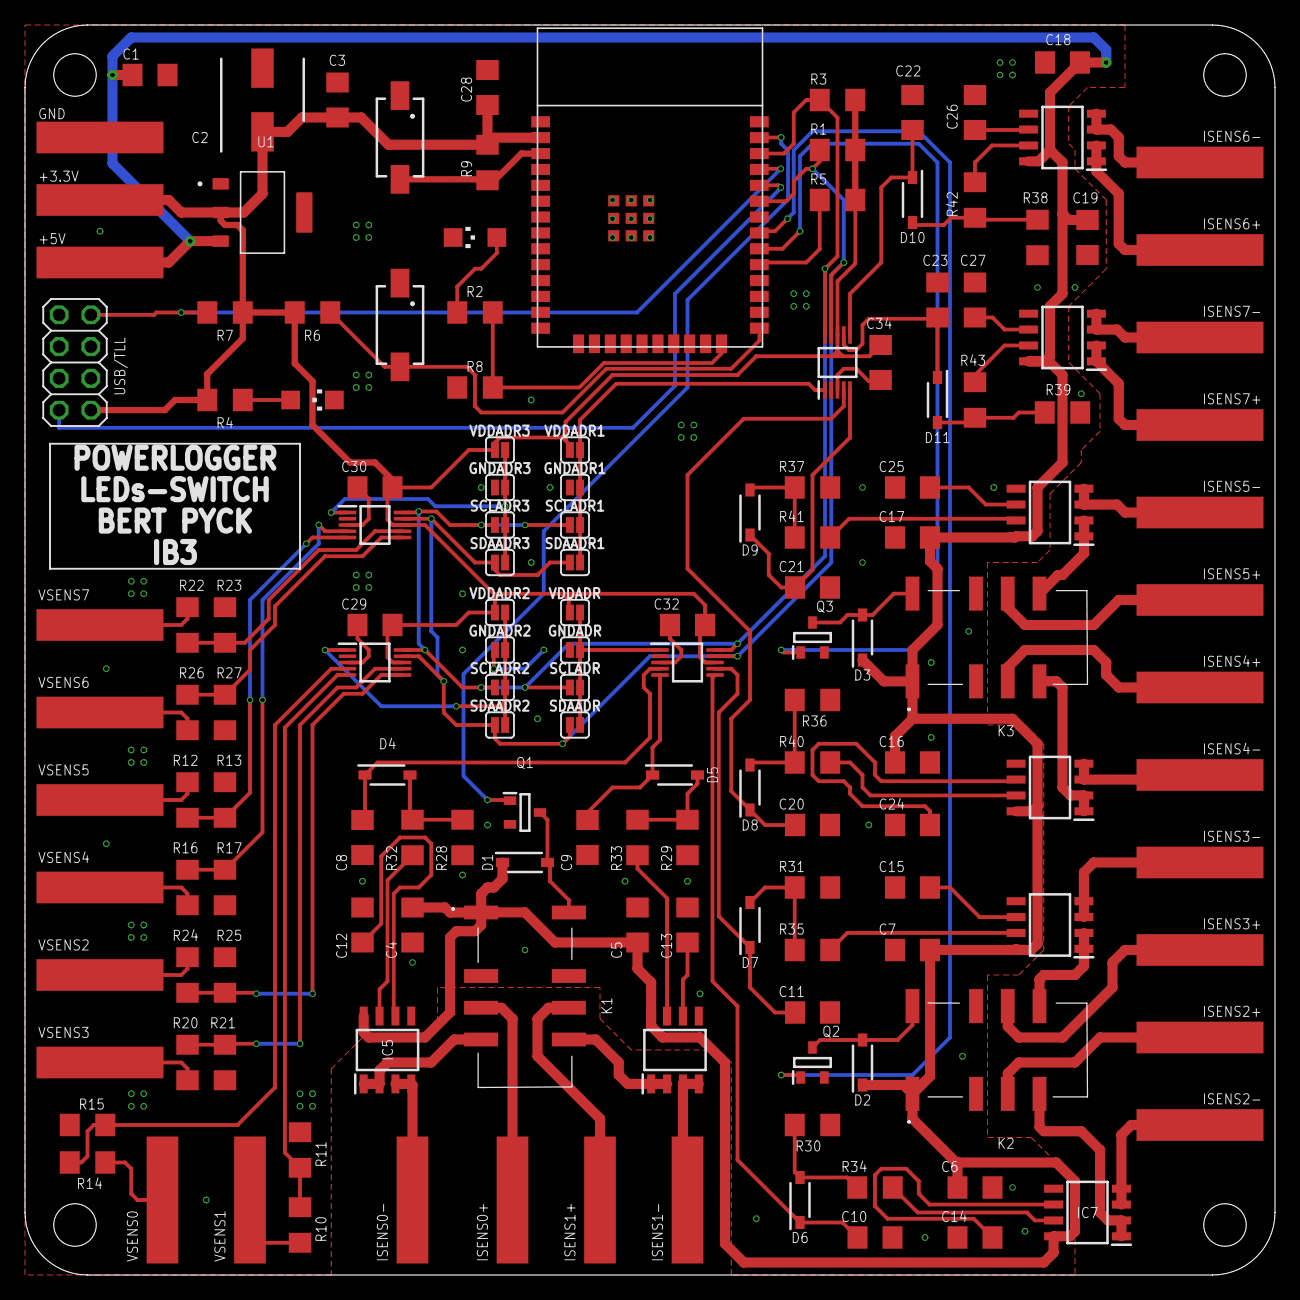
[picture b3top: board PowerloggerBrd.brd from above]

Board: 2 copper layers, 100.0 x 100.0 mm, 152 parts (0 on the bottom side), 93 nets.

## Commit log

2024-05-18 initialise
2024-05-18 initialise logboek
2024-05-18 initialise inhoud logboek
2024-05-18 intialise images
2024-05-18 initialise plantensensor
2024-05-18 intialise
2024-05-18 intiliase aquamonitoring
2024-05-18 intialise aansturing leds
2024-05-18 intialise image
2024-05-18 init leds
2024-05-18 initialise energiemonitoring
2024-05-23 VF IB3 update
2024-05-23 update aqua
2024-05-23 update dashboard
2024-05-23 update engergiemonitoring
2024-05-23 update logboek
2024-05-23 update operation
2024-05-23 update opera
2024-05-24 Revert "delete all to fork"
    This reverts commit 2d5b96d703e90744c07c19ecfc6bb0d3bed4118e.
2024-05-24 update aquamonitoring
2024-05-24 update energiemonitoring
2024-05-24 update leds
2024-05-24 update logbook
2024-05-24 update modularity
2024-05-24 update plantensensor
2024-05-24 update homepage
2024-05-24 make all links point to new github
2024-05-24 Adding last picture
2024-05-24 mistakes modularity
2024-05-24 mistake

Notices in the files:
parts and their libraries:
SparkFun-Jumpers: Licensing: Creative Commons ShareAlike 4.0 International - https://creativecommons.org/licenses/by-sa/4.0
